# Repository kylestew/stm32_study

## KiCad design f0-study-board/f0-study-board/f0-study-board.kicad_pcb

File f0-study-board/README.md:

# STM32 F0 Study Board

Simple MCU breakout for building study code samples.

## Parts

| Part      |                           |
|---------------------------------------|
| MCU       | STM32F091CBT6             |

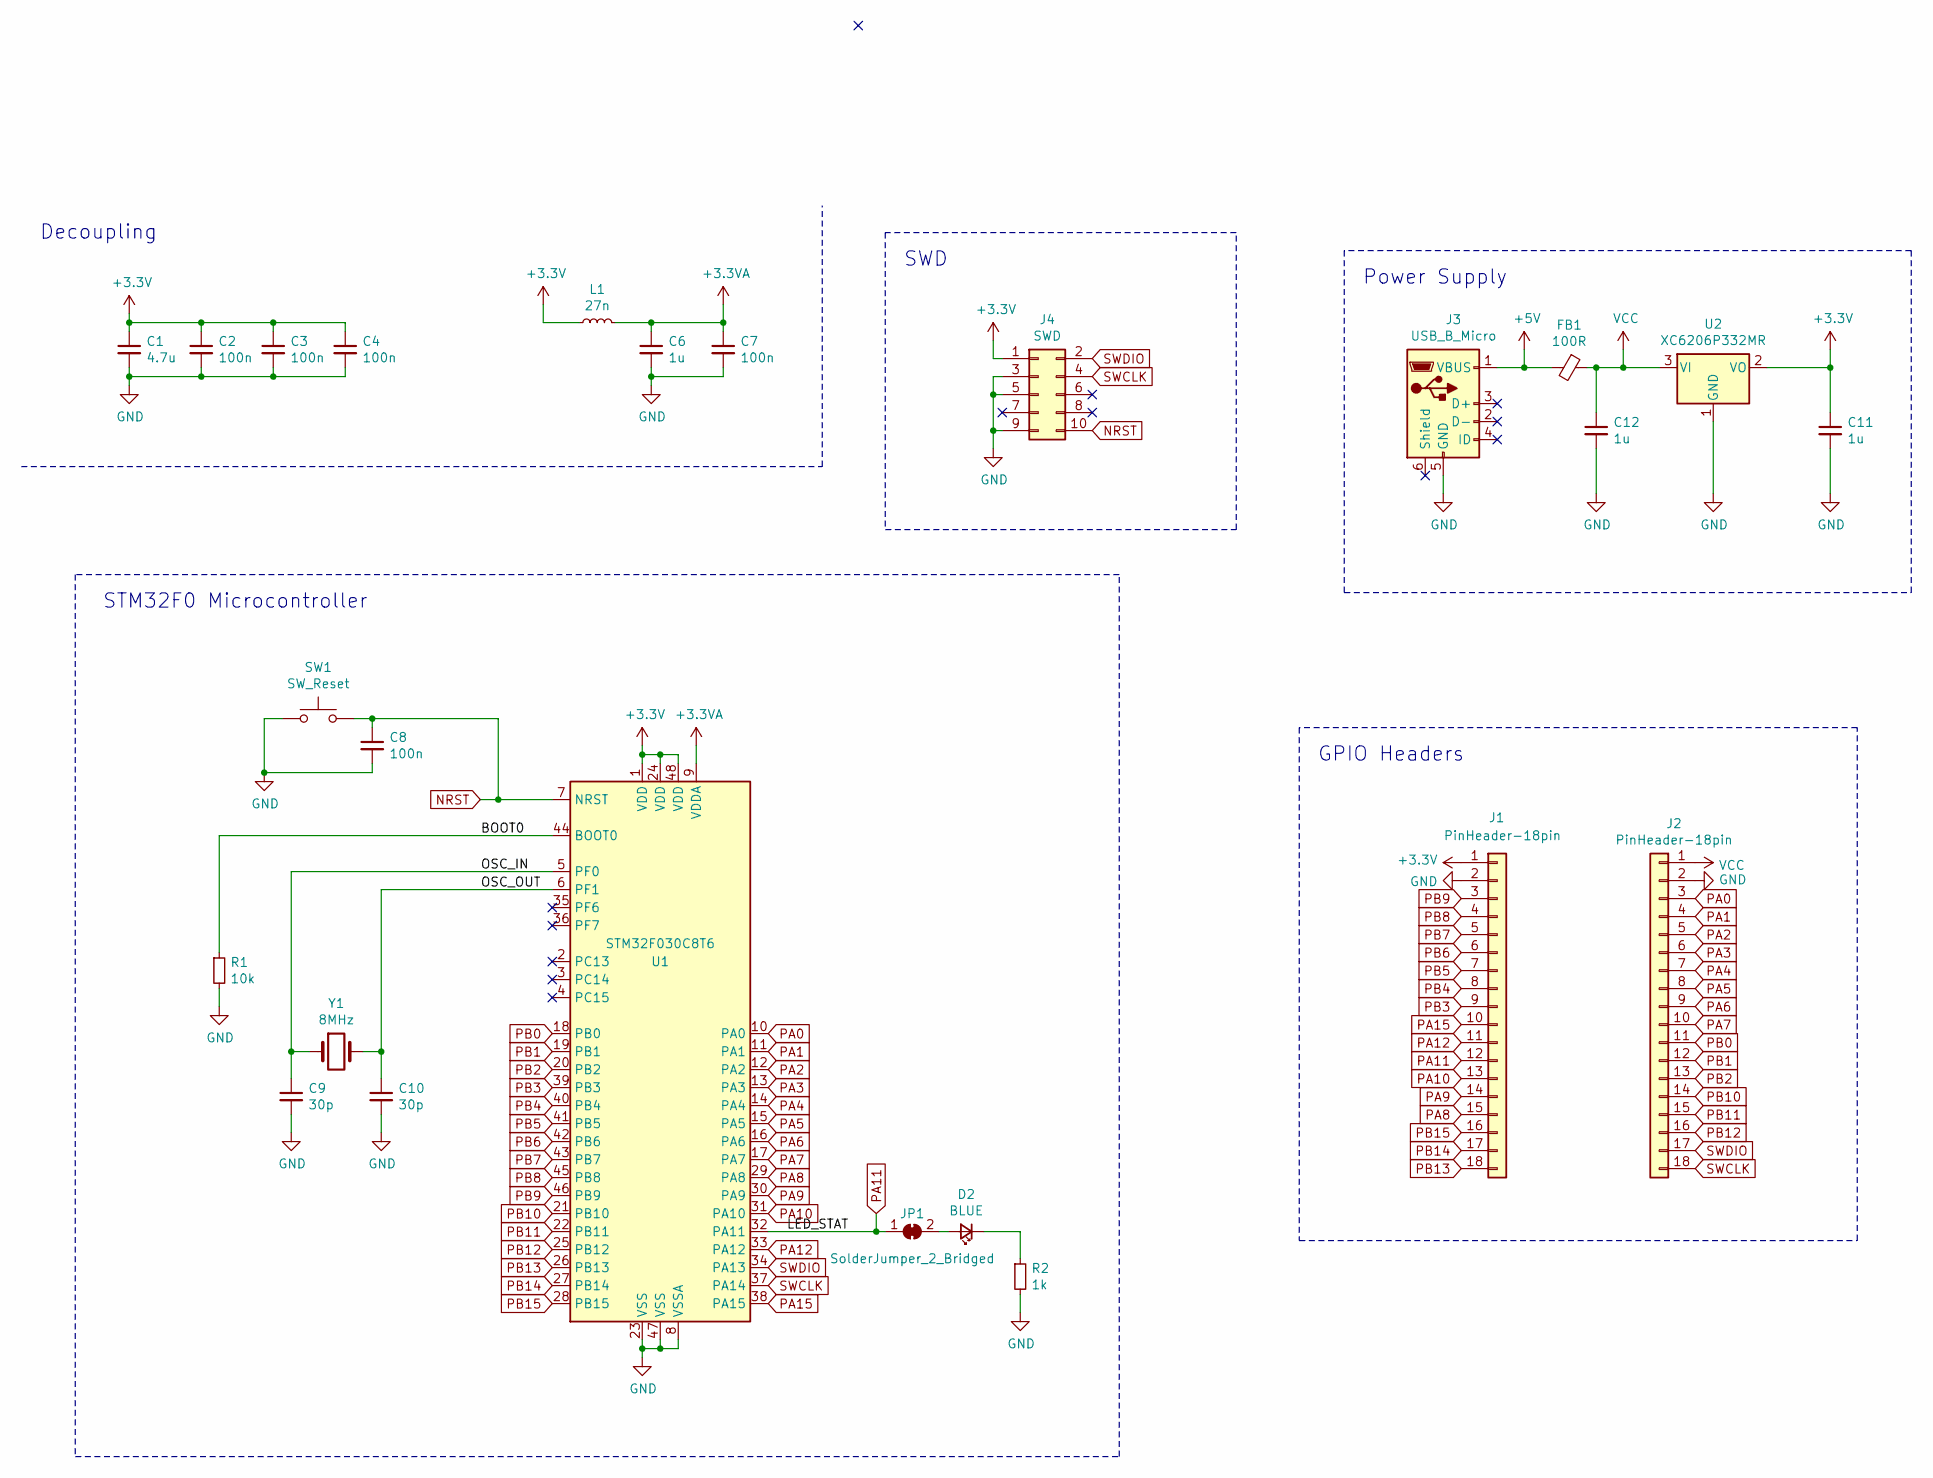
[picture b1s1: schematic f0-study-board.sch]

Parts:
C1: 4.7u; C_0805_2012Metric; LCSC Part # C1779
C2, C3, C4, C7, C8: 100n; C_0402_1005Metric; LCSC Part # C307331
C6: 1u; C_0402_1005Metric; LCSC Part # C52923
C9, C10: 30p; C_0402_1005Metric; LCSC Part # C1570
C11, C12: 1u; C_0805_2012Metric; LCSC Part # C28323
D2: BLUE; LED_0603_1608Metric; LCSC Part # C72041
FB1: 100R; L_0603_1608Metric; LCSC Part # C74325
J1, J2: PinHeader-18pin; PinHeader_1x18_P2.54mm_Vertical
J3: USB_B_Micro; USB_Micro-B_Molex_47346-0001; LCSC Part # C132560
J4: SWD; PinHeader_2x05_P1.27mm_Vertical_SMD
JP1: SolderJumper_2_Bridged; SolderJumper-2_P1.3mm_Bridged_Pad1.0x1.5mm
L1: 27n; L_0402_1005Metric; LCSC Part # C18830
R1: 10k; R_0402_1005Metric; LCSC Part # C25744
R2: 1k; R_0402_1005Metric; LCSC Part # C11702
SW1: SW_Reset; SW_Push_SPST_NO_Alps_SKRK; LCSC Part # C115357
U1: STM32F030C8T6; LQFP-48_7x7mm_P0.5mm; LCSC Part # C23922
U2: XC6206P332MR; SOT-23; LCSC Part # C5446
Y1: 8MHz; Crystal_SMD_5032-2Pin_5.0x3.2mm; LCSC Part # C115962

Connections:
+3.3VA: C6.1, C7.1, L1.2, U1.9 (VDDA)
+3V3: C1.1, C2.1, C3.1, C4.1, C11.1, J1.1, J4.1, L1.1, U1.1 (VDD), U1.24 (VDD), U1.48 (VDD), U2.2 (VO)
+5V: FB1.2, J3.1 (VBUS)
/BOOT0: R1.1, U1.44 (BOOT0)
/OSC_IN: C9.1, U1.5 (PF0), Y1.1
/OSC_OUT: C10.1, U1.6 (PF1), Y1.2
GND: C1.2, C2.2, C3.2, C4.2, C6.2, C7.2, C8.2, C9.2, C10.2, C11.2, C12.2, J1.2, J2.2, J3.5 (GND), J4.3, J4.5, J4.9, R1.2, R2.2, SW1.1, U1.8 (VSSA), U1.23 (VSS), U1.47 (VSS), U2.1 (GND)
NRST: C8.1, J4.10, SW1.2, U1.7 (NRST)
unnamed: D2.1 (K), R2.1
unnamed: D2.2 (A), JP1.2 (B)
PA0: J2.3, U1.10 (PA0)
PA1: J2.4, U1.11 (PA1)
PA2: J2.5, U1.12 (PA2)
PA3: J2.6, U1.13 (PA3)
PA4: J2.7, U1.14 (PA4)
PA5: J2.8, U1.15 (PA5)
PA6: J2.9, U1.16 (PA6)
PA7: J2.10, U1.17 (PA7)
PA8: J1.15, U1.29 (PA8)
PA9: J1.14, U1.30 (PA9)
PA10: J1.13, U1.31 (PA10)
PA11: J1.12, JP1.1 (A), U1.32 (PA11)
PA12: J1.11, U1.33 (PA12)
PA15: J1.10, U1.38 (PA15)
PB0: J2.11, U1.18 (PB0)
PB1: J2.12, U1.19 (PB1)
PB2: J2.13, U1.20 (PB2)
PB3: J1.9, U1.39 (PB3)
PB4: J1.8, U1.40 (PB4)
PB5: J1.7, U1.41 (PB5)
PB6: J1.6, U1.42 (PB6)
PB7: J1.5, U1.43 (PB7)
PB8: J1.4, U1.45 (PB8)
PB9: J1.3, U1.46 (PB9)
PB10: J2.14, U1.21 (PB10)
PB11: J2.15, U1.22 (PB11)
PB12: J2.16, U1.25 (PB12)
PB13: J1.18, U1.26 (PB13)
PB14: J1.17, U1.27 (PB14)
PB15: J1.16, U1.28 (PB15)
SWCLK: J2.18, J4.4, U1.37 (PA14)
SWDIO: J2.17, J4.2, U1.34 (PA13)
VCC: C12.1, FB1.1, J2.1, U2.3 (VI)

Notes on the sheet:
Decoupling
STM32F0 Microcontroller
GPIO Headers
Power Supply
SWD

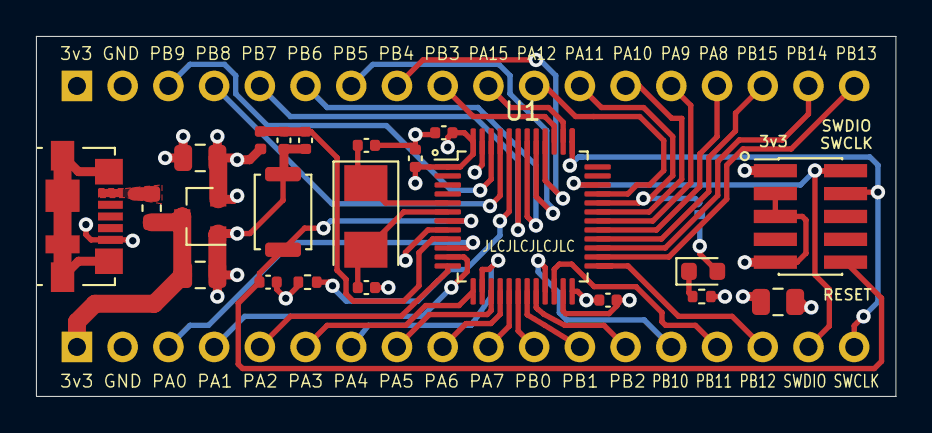
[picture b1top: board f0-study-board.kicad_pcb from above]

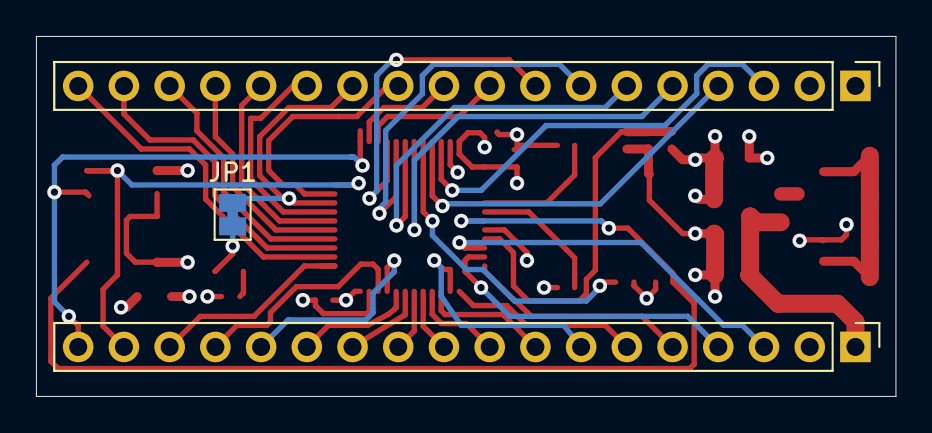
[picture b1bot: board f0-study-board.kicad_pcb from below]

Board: 4 copper layers, 47.8 x 20.0 mm, 25 parts (3 on the bottom side), 43 nets.

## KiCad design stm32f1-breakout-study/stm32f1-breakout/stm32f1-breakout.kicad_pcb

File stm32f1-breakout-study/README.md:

# PCB Design Study

https://github.com/pms67/STM32F1-Breakout-Board

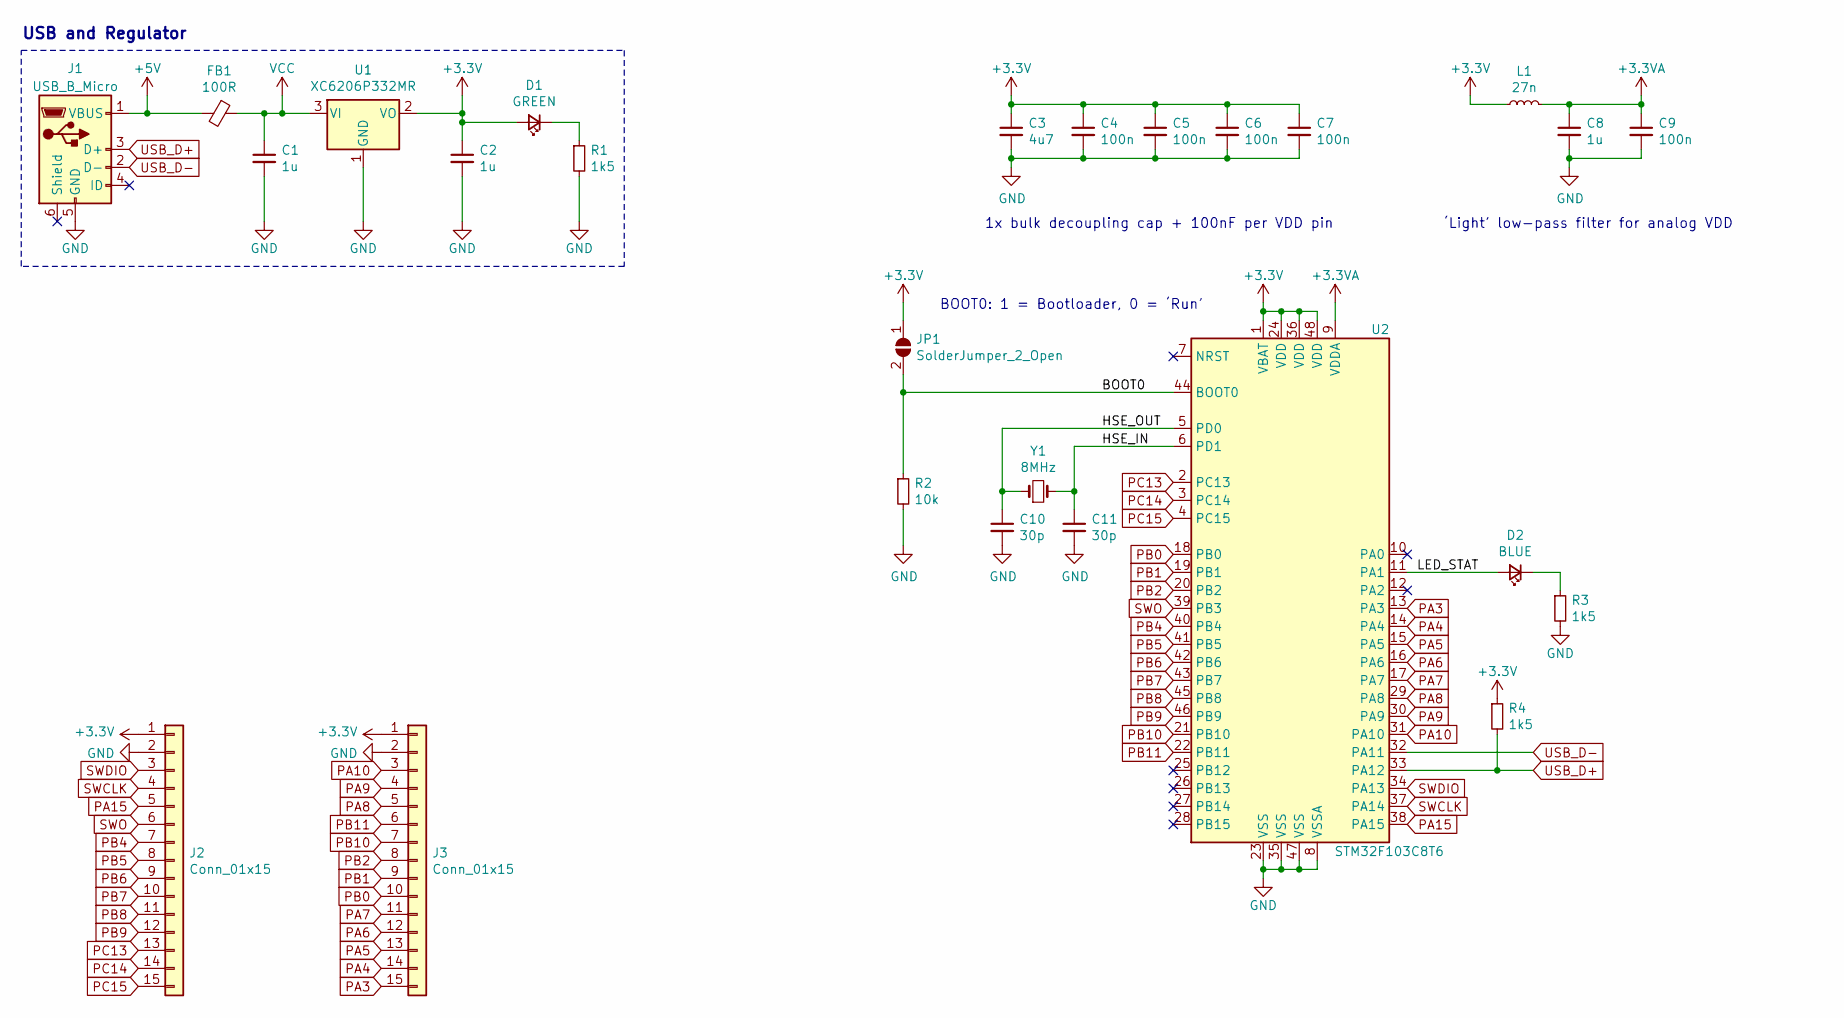
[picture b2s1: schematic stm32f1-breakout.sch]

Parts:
C1, C2: 1u; C_0603_1608Metric
C3: 4u7; C_0603_1608Metric
C4, C5, C6, C7, C9: 100n; C_0402_1005Metric
C8: 1u; C_0402_1005Metric
C10, C11: 30p; C_0402_1005Metric
D1: GREEN; LED_0603_1608Metric
D2: BLUE; LED_0603_1608Metric
FB1: 100R; L_0805_2012Metric
J1: USB_B_Micro; USB_Micro-B_Wuerth_629105150521
J2, J3: Conn_01x15; PinHeader_1x15_P2.54mm_Vertical
JP1: SolderJumper_2_Open; SolderJumper-2_P1.3mm_Open_Pad1.0x1.5mm
L1: 27n; L_0402_1005Metric
R1, R3: 1k5; R_0603_1608Metric
R2: 10k; R_0402_1005Metric
R4: 1k5; R_0402_1005Metric
U1: XC6206P332MR; SOT-23
U2: STM32F103C8T6; LQFP-48_7x7mm_P0.5mm
Y1: 8MHz; Crystal_SMD_5032-2Pin_5.0x3.2mm

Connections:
+3.3VA: C8.1, C9.1, L1.2, U2.9 (VDDA)
+3V3: C2.1, C3.1, C4.1, C5.1, C6.1, C7.1, D1.2 (A), J2.1, J3.1, JP1.1 (A), L1.1, R4.1, U1.2 (VO), U2.1 (VBAT), U2.24 (VDD), U2.36 (VDD), U2.48 (VDD)
+5V: FB1.2, J1.1 (VBUS)
/BOOT0: JP1.2 (B), R2.1, U2.44 (BOOT0)
/HSE_IN: C11.1, U2.6 (PD1), Y1.2
/HSE_OUT: C10.1, U2.5 (PD0), Y1.1
/LED_STAT: D2.2 (A), U2.11 (PA1)
GND: C1.2, C2.2, C3.2, C4.2, C5.2, C6.2, C7.2, C8.2, C9.2, C10.2, C11.2, J1.5 (GND), J2.2, J3.2, R1.2, R2.2, R3.2, U1.1 (GND), U2.8 (VSSA), U2.23 (VSS), U2.35 (VSS), U2.47 (VSS)
unnamed: D1.1 (K), R1.1
unnamed: D2.1 (K), R3.1
PA3: J3.15, U2.13 (PA3)
PA4: J3.14, U2.14 (PA4)
PA5: J3.13, U2.15 (PA5)
PA6: J3.12, U2.16 (PA6)
PA7: J3.11, U2.17 (PA7)
PA8: J3.5, U2.29 (PA8)
PA9: J3.4, U2.30 (PA9)
PA10: J3.3, U2.31 (PA10)
PA15: J2.5, U2.38 (PA15)
PB0: J3.10, U2.18 (PB0)
PB1: J3.9, U2.19 (PB1)
PB2: J3.8, U2.20 (PB2)
PB4: J2.7, U2.40 (PB4)
PB5: J2.8, U2.41 (PB5)
PB6: J2.9, U2.42 (PB6)
PB7: J2.10, U2.43 (PB7)
PB8: J2.11, U2.45 (PB8)
PB9: J2.12, U2.46 (PB9)
PB10: J3.7, U2.21 (PB10)
PB11: J3.6, U2.22 (PB11)
PC13: J2.13, U2.2 (PC13)
PC14: J2.14, U2.3 (PC14)
PC15: J2.15, U2.4 (PC15)
SWCLK: J2.4, U2.37 (PA14)
SWDIO: J2.3, U2.34 (PA13)
SWO: J2.6, U2.39 (PB3)
USB_D+: J1.3 (D+), R4.2, U2.33 (PA12)
USB_D-: J1.2 (D-), U2.32 (PA11)
VCC: C1.1, FB1.1, U1.3 (VI)

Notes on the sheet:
USB and Regulator
1x bulk decoupling cap + 100nF per VDD pin
‘Light’ low-pass filter for analog VDD
BOOT0: 1 = Bootloader, 0 = ‘Run’

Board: 2 copper layers, 26 parts (0 on the bottom side), 39 nets, no tracks yet.

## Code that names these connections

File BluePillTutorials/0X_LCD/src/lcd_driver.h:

#pragma once

#include "stm32f1xx.h"


// 5V tollerant
/*
8 bit char D0-D7
PB8
PB9
PB10
PB11
PB12
PB13
PB14
PB15

EN: PA8
RW: PA9
Reg Sel: PA10
*/
#define LCD_CONTROL_PORT  GPIOA
#define LCD_EN            8
#define LCD_RW            9
#define LCDRS             10

void lcd_init() {
  // Enable LCD Control Port
  RCC->APB2ENR |= RCC_APB2ENR_IOPAEN;

  // Enable LCD Data Port
  RCC->APB2ENR |= RCC_APB2ENR_IOPBEN;

  // Setup PA 8, 9, 10 to output with 10 MHz speed
  GPIOA->CRH = 0b000100010001;

  // Setup PB8-PB15 as output with 10 MHz speed
  // CNF/MODE bits are in word pairs: CNF1,CNF0,MODE1,MODE0 * 8 = 32 bits
  GPIOB->CRH = 0b00010001000100010001000100010001;
}

void delay(int timeDelay) {
  for (int i = 0; i < timeDelay; i++) {}
}

void enableWrite() {
  LCD_CONTROL_PORT->BSRR &= ~(1 << LCD_RW);
  delay(40000);
}

void enableRead() {
  LCD_CONTROL_PORT->BSRR |= (1 << LCD_RW);
  delay(40000);
}

void commandMode() {
  LCD_CONTROL_PORT->BSRR &= ~(1 << LCD_RS);
  delay(40000);
}

void characterMode() {
  LCD_CONTROL_PORT->BSRR |= (1 << LCD_RS);
  delay(40000);
}

void lcd_send_character(char character) {
  // Toggle EN to 0
  LCD_CONTROL_PORT->BSRR &= ~(1 << LCD_EN);

  delay(80000);


  // Turn on PB8-PB15
  // GPIOB->BSRR = 0b1111111100000000;

  // Send character "A" to PB8-15
  GPIOB->BSRR = character<<8;

  // GPIOA->BSRR = 0b101<<8;
}

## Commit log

2021-07-18 Combine existing repos
2021-07-19 Board shem and non-routed layout
2021-07-20 Routed the board, ready for export
2021-07-20 Had to choose another mcu
2021-07-20 Board gerbers sent
2021-07-23 Following along with Vivonomicon blog
2021-07-24 Cheating and using PIO to access CMSIS without a bunch of headache, just need to get to work
